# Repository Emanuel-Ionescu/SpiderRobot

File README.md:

## SpiderRobot

Check software and hardware branch

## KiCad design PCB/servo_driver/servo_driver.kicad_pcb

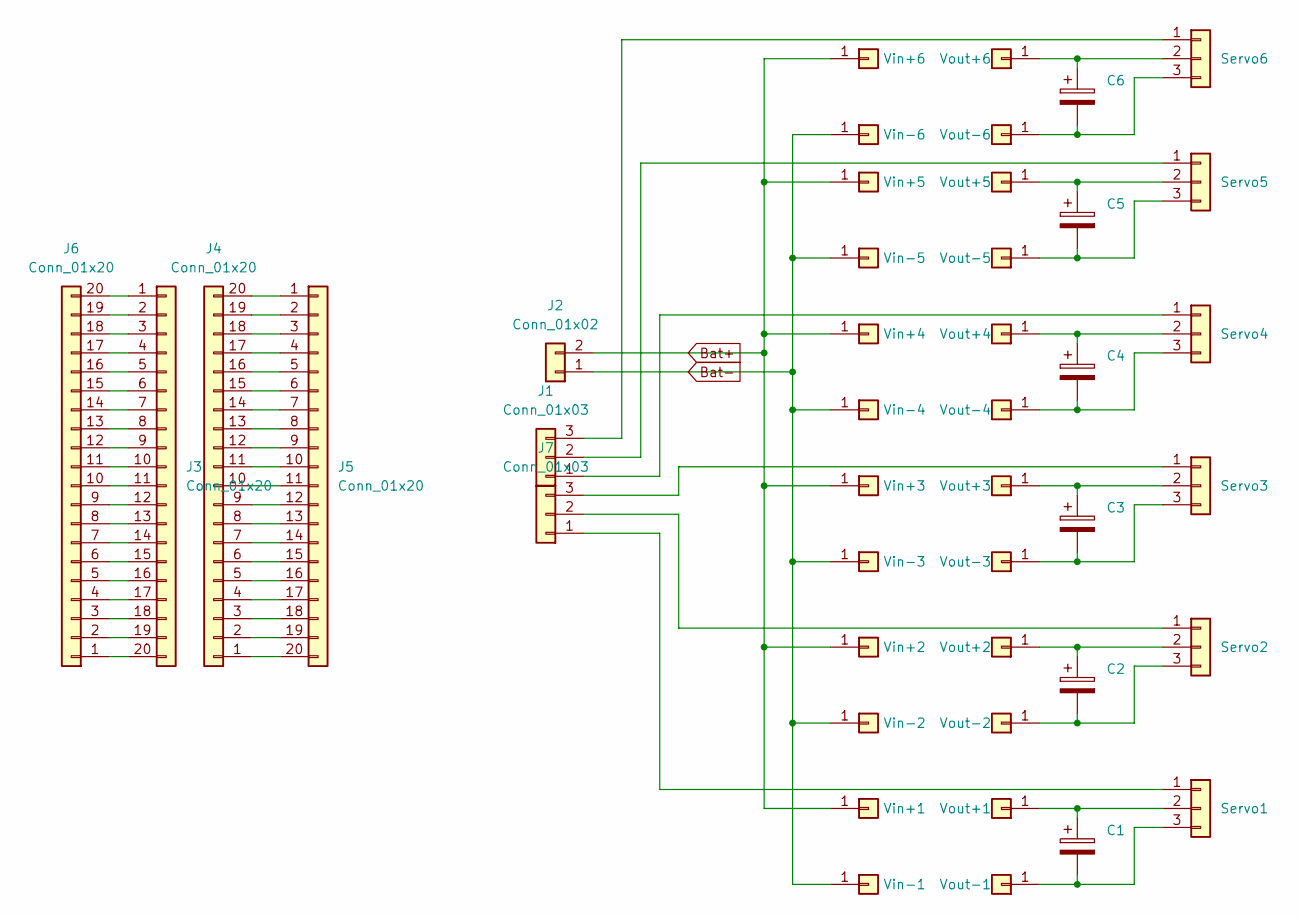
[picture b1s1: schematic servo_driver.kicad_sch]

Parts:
C1, C2, C3, C4, C5, C6: C_Polarized; CP_Radial_D5.0mm_P2.50mm
J1, J7: Conn_01x03; JST_PH_B3B-PH-K_1x03_P2.00mm_Vertical
J2: Conn_01x02; AMASS_XT60-M_1x02_P7.20mm_Vertical
J3, J4, J5, J6: Conn_01x20; PinHeader_1x20_P2.54mm_Vertical
Servo1, Servo2, Servo3, Servo4, Servo5, Servo6: Conn_01x03; PinSocket_1x03_P2.54mm_Vertical
Vin+1, Vin+2, Vin+3, Vin+4, Vin+5, Vin+6: Conn_01x01; PinHeader_1x01_P2.00mm_Vertical
Vin-1, Vin-2, Vin-3, Vin-4, Vin-5, Vin-6: Conn_01x01; PinHeader_1x01_P2.00mm_Vertical
Vout+1, Vout+2, Vout+3, Vout+4, Vout+5, Vout+6: Conn_01x01; PinHeader_1x01_P2.00mm_Vertical
Vout-1, Vout-2, Vout-3, Vout-4, Vout-5, Vout-6: Conn_01x01; PinHeader_1x01_P2.00mm_Vertical

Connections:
Bat+: J2.2, Vin+1.1, Vin+2.1, Vin+3.1, Vin+4.1, Vin+5.1, Vin+6.1
Bat-: J2.1, Vin-1.1, Vin-2.1, Vin-3.1, Vin-4.1, Vin-5.1, Vin-6.1
unnamed: J1.1, Servo4.1
unnamed: J1.2, Servo5.1
unnamed: J1.3, Servo6.1
unnamed: J3.1, J6.20
unnamed: J3.2, J6.19
unnamed: J3.3, J6.18
unnamed: J3.4, J6.17
unnamed: J3.5, J6.16
unnamed: J3.6, J6.15
unnamed: J3.7, J6.14
unnamed: J3.8, J6.13
unnamed: J3.9, J6.12
unnamed: J3.10, J6.11
unnamed: J3.11, J6.10
unnamed: J3.12, J6.9
unnamed: J3.13, J6.8
unnamed: J3.14, J6.7
unnamed: J3.15, J6.6
unnamed: J3.16, J6.5
unnamed: J3.17, J6.4
unnamed: J3.18, J6.3
unnamed: J3.19, J6.2
unnamed: J3.20, J6.1
unnamed: J4.1, J5.20
unnamed: J4.2, J5.19
unnamed: J4.3, J5.18
unnamed: J4.4, J5.17
unnamed: J4.5, J5.16
unnamed: J4.6, J5.15
unnamed: J4.7, J5.14
unnamed: J4.8, J5.13
unnamed: J4.9, J5.12
unnamed: J4.10, J5.11
unnamed: J4.11, J5.10
unnamed: J4.12, J5.9
unnamed: J4.13, J5.8
unnamed: J4.14, J5.7
unnamed: J4.15, J5.6
unnamed: J4.16, J5.5
unnamed: J4.17, J5.4
unnamed: J4.18, J5.3
unnamed: J4.19, J5.2
unnamed: J4.20, J5.1
unnamed: J7.1, Servo1.1
unnamed: J7.2, Servo2.1
unnamed: J7.3, Servo3.1
unnamed: C1.1, Servo1.2, Vout+1.1
unnamed: C1.2, Servo1.3, Vout-1.1
unnamed: C2.1, Servo2.2, Vout+2.1
unnamed: C2.2, Servo2.3, Vout-2.1
unnamed: C3.1, Servo3.2, Vout+3.1
unnamed: C3.2, Servo3.3, Vout-3.1
unnamed: C4.1, Servo4.2, Vout+4.1
unnamed: C4.2, Servo4.3, Vout-4.1
unnamed: C5.1, Servo5.2, Vout+5.1
unnamed: C5.2, Servo5.3, Vout-5.1
unnamed: C6.1, Servo6.2, Vout+6.1
unnamed: C6.2, Servo6.3, Vout-6.1

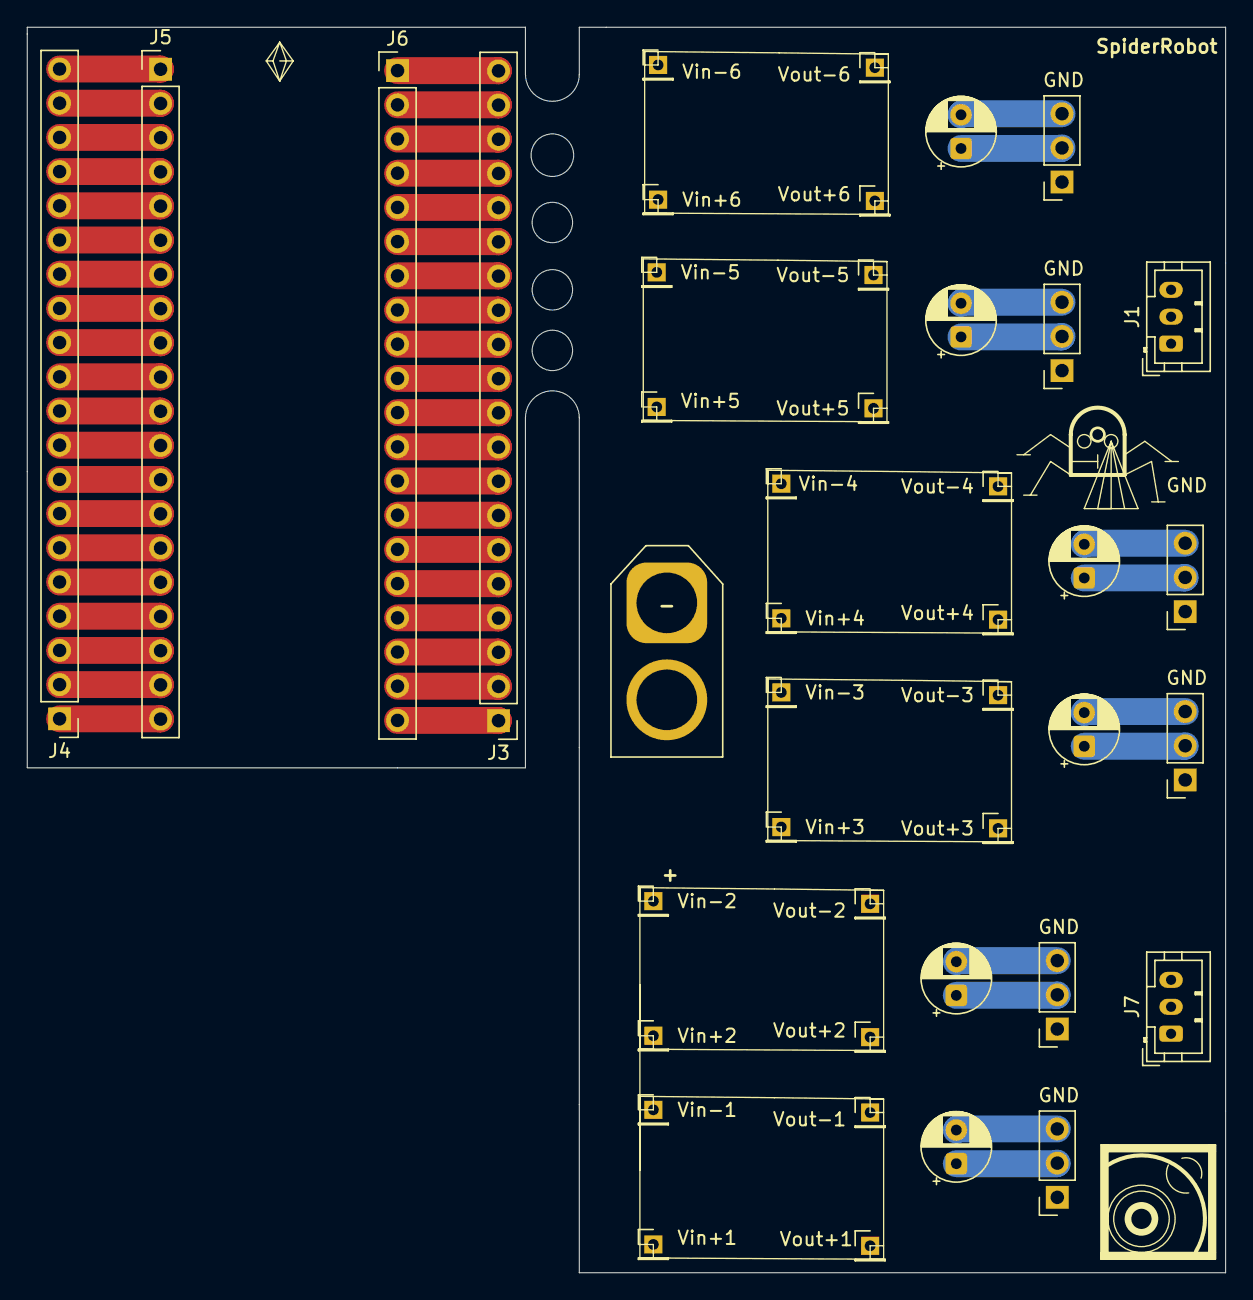
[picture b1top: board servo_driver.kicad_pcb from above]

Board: 2 copper layers, 89.0 x 92.5 mm, 43 parts (0 on the bottom side), 60 nets.

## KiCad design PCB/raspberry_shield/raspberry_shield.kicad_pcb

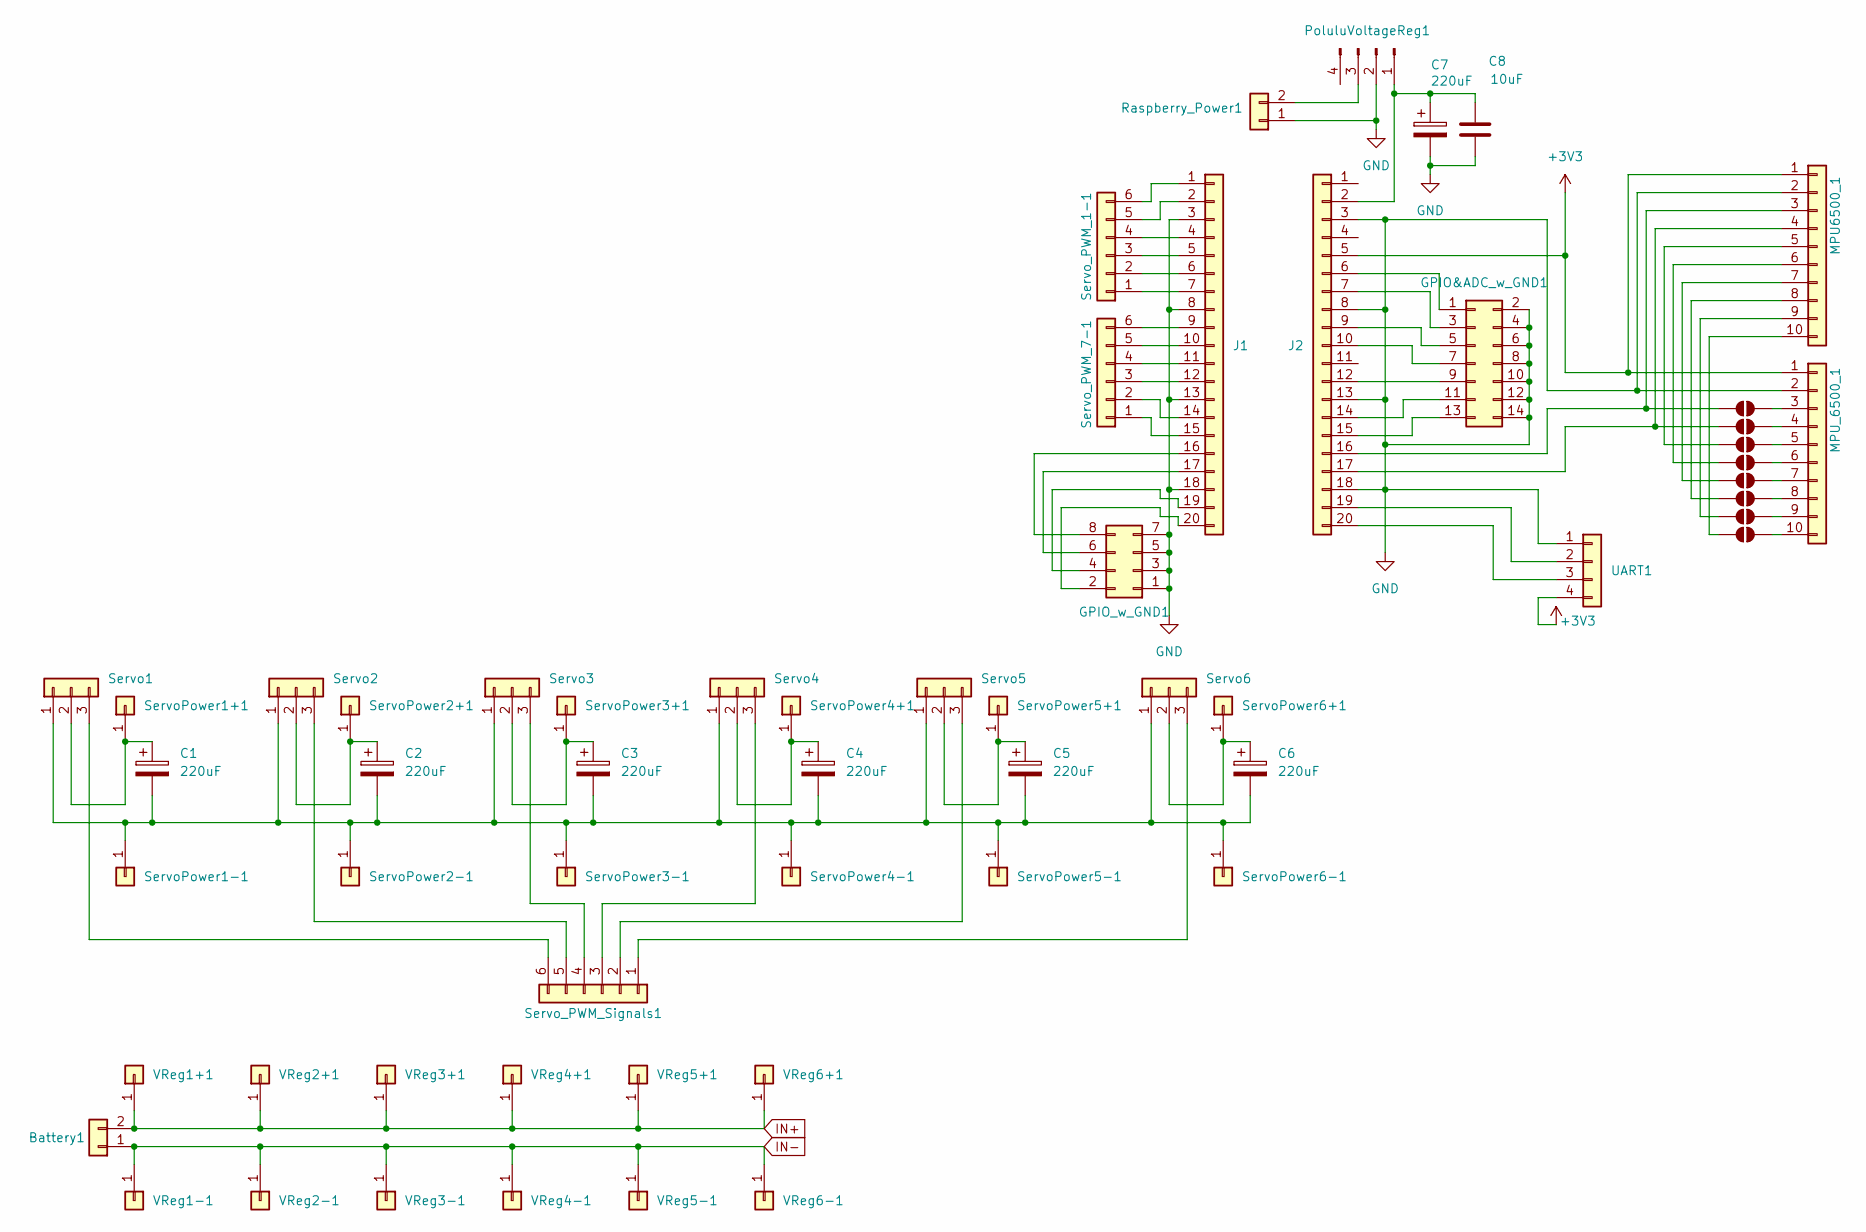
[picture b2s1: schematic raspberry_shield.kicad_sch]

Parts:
Battery1: Conn_01x02; AMASS_XT60-M_1x02_P7.20mm_Vertical
C1, C2, C3, C4, C5, C6, C7: 220uF; CP_Radial_D5.0mm_P2.50mm
C8: 10uF; C_0603_1608Metric
GPIO&ADC_w_GND1: Conn_02x07_Odd_Even; PinHeader_2x07_P2.54mm_Vertical
GPIO_w_GND1: Conn_02x04_Odd_Even; PinSocket_2x04_P2.54mm_Vertical
J1, J2: PinSocket_1x20_P2.54mm_Vertical
JP1, JP2, JP3, JP4, JP5, JP6, JP7, JP8: SolderJumper_2_Open; SolderJumper-2_P1.3mm_Open_RoundedPad1.0x1.5mm
MPU6500_1: Conn_01x10; PinHeader_1x10_P2.54mm_Vertical
MPU_6500_1: Conn_01x10; PinHeader_1x10_P2.54mm_Vertical
PoluluVoltageReg1: Voltage Reg; PinHeader_1x04_P2.54mm_Vertical
Raspberry_Power1: Conn_01x02; PinHeader_1x02_P2.54mm_Vertical
Servo1, Servo2, Servo3, Servo4, Servo5, Servo6: Conn_01x03; PinHeader_1x03_P2.54mm_Vertical
ServoPower1+1, ServoPower1-1, ServoPower2+1, ServoPower2-1, ServoPower3+1, ServoPower3-1, ServoPower4+1, ServoPower4-1, ServoPower5+1, ServoPower5-1, ServoPower6+1, ServoPower6-1: Conn_01x01; PinHeader_1x01_P2.54mm_Vertical
Servo_PWM_1-1: Conn_01x06; PinSocket_1x06_P2.54mm_Vertical
Servo_PWM_7-1: Servo_Signals_7-12; PinSocket_1x06_P2.54mm_Vertical
Servo_PWM_Signals1: Conn_01x06; PinSocket_1x06_P2.54mm_Vertical
UART1: Conn_01x04; PinHeader_1x04_P2.54mm_Vertical
VReg1+1, VReg1-1, VReg2+1, VReg2-1, VReg3+1, VReg3-1, VReg4+1, VReg4-1, VReg5+1, VReg5-1, VReg6+1, VReg6-1: Conn_01x01; PinHeader_1x01_P2.54mm_Vertical

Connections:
+3V3: J2.5, MPU6500_1.1, MPU_6500_1.1, UART1.4
GND: C7.2, C8.2, GPIO&ADC_w_GND1.2, GPIO&ADC_w_GND1.4, GPIO&ADC_w_GND1.6, GPIO&ADC_w_GND1.8, GPIO&ADC_w_GND1.10, GPIO&ADC_w_GND1.12, GPIO&ADC_w_GND1.14, GPIO_w_GND1.1, GPIO_w_GND1.3, GPIO_w_GND1.5, GPIO_w_GND1.7, J1.3, J1.8, J1.13, J1.18, J2.3, J2.8, J2.13, J2.18, MPU6500_1.2, MPU_6500_1.2, PoluluVoltageReg1.2, Raspberry_Power1.1, UART1.1
IN+: Battery1.2, VReg1+1.1, VReg2+1.1, VReg3+1.1, VReg4+1.1, VReg5+1.1, VReg6+1.1
IN-: Battery1.1, VReg1-1.1, VReg2-1.1, VReg3-1.1, VReg4-1.1, VReg5-1.1, VReg6-1.1
unnamed: GPIO&ADC_w_GND1.1, J2.6
unnamed: GPIO&ADC_w_GND1.3, J2.7
unnamed: GPIO&ADC_w_GND1.5, J2.9
unnamed: GPIO&ADC_w_GND1.7, J2.10
unnamed: GPIO&ADC_w_GND1.9, J2.12
unnamed: GPIO&ADC_w_GND1.11, J2.14
unnamed: GPIO&ADC_w_GND1.13, J2.15
unnamed: GPIO_w_GND1.2, J1.20
unnamed: GPIO_w_GND1.4, J1.19
unnamed: GPIO_w_GND1.6, J1.17
unnamed: GPIO_w_GND1.8, J1.16
unnamed: J1.1, Servo_PWM_1-1.6
unnamed: J1.2, Servo_PWM_1-1.5
unnamed: J1.4, Servo_PWM_1-1.4
unnamed: J1.5, Servo_PWM_1-1.3
unnamed: J1.6, Servo_PWM_1-1.2
unnamed: J1.7, Servo_PWM_1-1.1
unnamed: J1.9, Servo_PWM_7-1.6
unnamed: J1.10, Servo_PWM_7-1.5
unnamed: J1.11, Servo_PWM_7-1.4
unnamed: J1.12, Servo_PWM_7-1.3
unnamed: J1.14, Servo_PWM_7-1.2
unnamed: J1.15, Servo_PWM_7-1.1
unnamed: C7.1, C8.1, J2.2, PoluluVoltageReg1.1
unnamed: J2.16, JP1.1 (A), MPU6500_1.3
unnamed: J2.17, JP2.1 (A), MPU6500_1.4
unnamed: J2.19, UART1.2
unnamed: J2.20, UART1.3
unnamed: JP1.2 (B), MPU_6500_1.3
unnamed: JP2.2 (B), MPU_6500_1.4
unnamed: JP3.1 (A), MPU6500_1.5
unnamed: JP3.2 (B), MPU_6500_1.5
unnamed: JP4.1 (A), MPU6500_1.6
unnamed: JP4.2 (B), MPU_6500_1.6
unnamed: JP5.1 (A), MPU6500_1.7
unnamed: JP5.2 (B), MPU_6500_1.7
unnamed: JP6.1 (A), MPU6500_1.8
unnamed: JP6.2 (B), MPU_6500_1.8
unnamed: JP7.1 (A), MPU6500_1.9
unnamed: JP7.2 (B), MPU_6500_1.9
unnamed: JP8.1 (A), MPU6500_1.10
unnamed: JP8.2 (B), MPU_6500_1.10
unnamed: PoluluVoltageReg1.3, Raspberry_Power1.2
unnamed: C1.2, C2.2, C3.2, C4.2, C5.2, C6.2, Servo1.1, Servo2.1, Servo3.1, Servo4.1, Servo5.1, Servo6.1, ServoPower1-1.1, ServoPower2-1.1, ServoPower3-1.1, ServoPower4-1.1, ServoPower5-1.1, ServoPower6-1.1
unnamed: C1.1, Servo1.2, ServoPower1+1.1
unnamed: Servo1.3, Servo_PWM_Signals1.6
unnamed: C2.1, Servo2.2, ServoPower2+1.1
unnamed: Servo2.3, Servo_PWM_Signals1.5
unnamed: C3.1, Servo3.2, ServoPower3+1.1
unnamed: Servo3.3, Servo_PWM_Signals1.4
unnamed: C4.1, Servo4.2, ServoPower4+1.1
unnamed: Servo4.3, Servo_PWM_Signals1.3
unnamed: C5.1, Servo5.2, ServoPower5+1.1
unnamed: Servo5.3, Servo_PWM_Signals1.2
unnamed: C6.1, Servo6.2, ServoPower6+1.1
unnamed: Servo6.3, Servo_PWM_Signals1.1

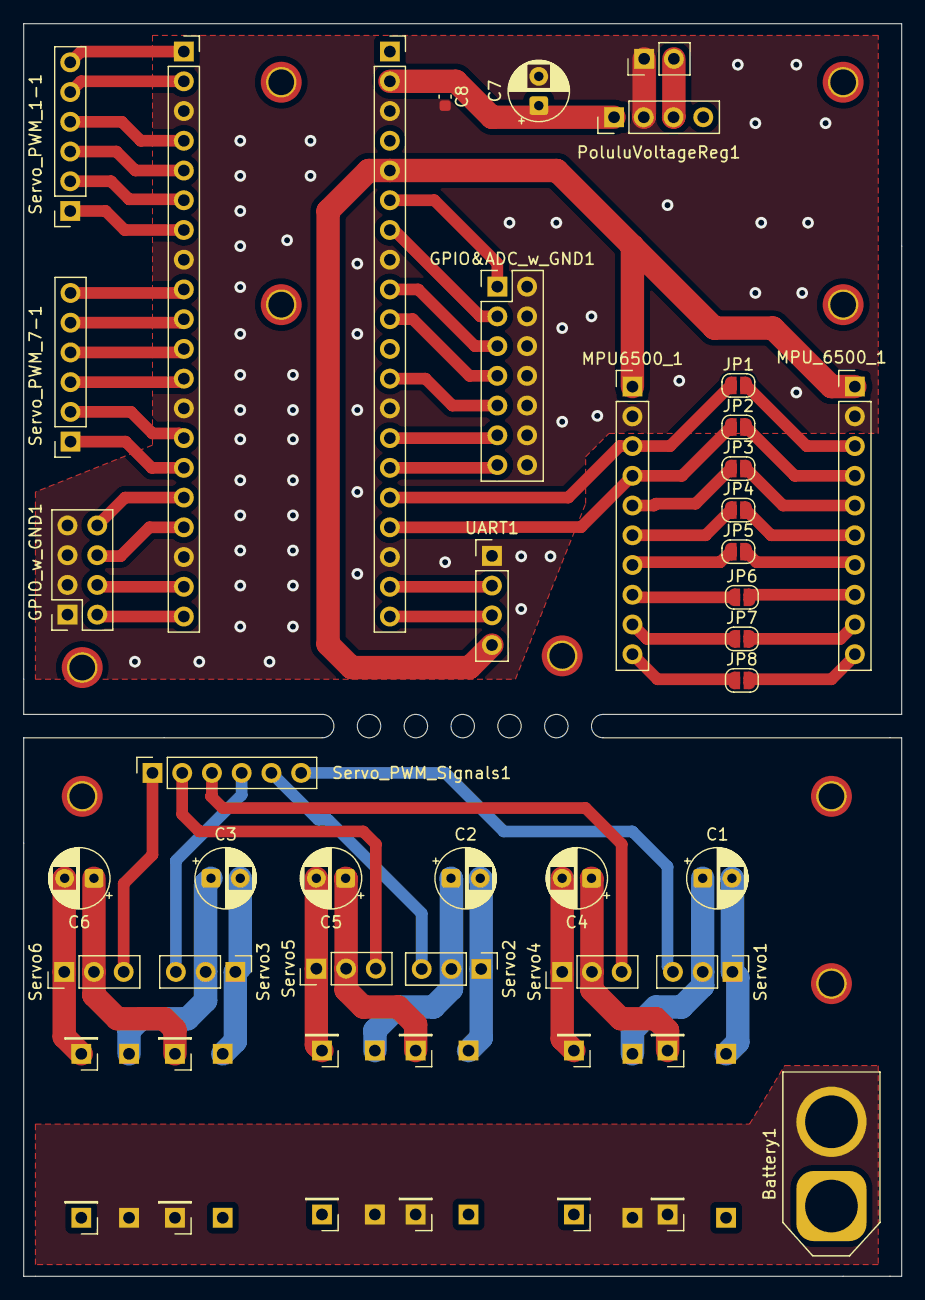
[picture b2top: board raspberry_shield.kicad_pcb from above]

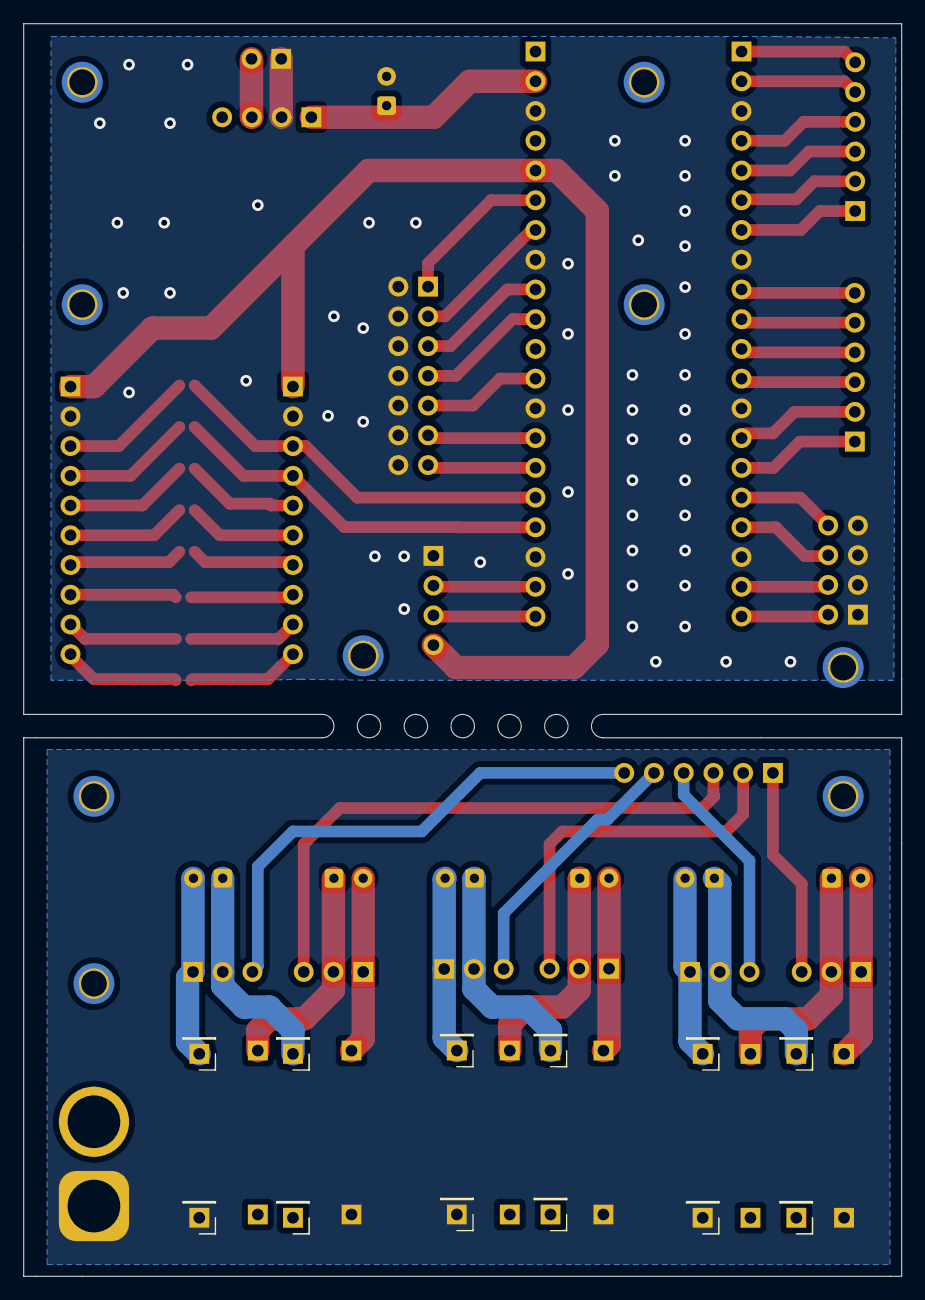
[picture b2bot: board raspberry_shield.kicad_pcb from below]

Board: 2 copper layers, 75.0 x 107.0 mm, 59 parts (12 on the bottom side), 60 nets.

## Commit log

2025-09-23 Inital Commit
2025-09-24 Manual Servo Control
2025-09-28 Manual control fixed
2025-09-29 Sequence feature start
2025-09-30 Remote control
2025-10-11 raspberry shield version 1
2025-10-11 Seqences with fixed positions
2025-11-08 Restructure of files
2025-12-03 Big Update
2025-12-03 3D models
2025-12-12 Serial comms
2025-12-12 updated hardware
2025-12-12 Branch for hardware
2025-12-12 Software branch
2025-12-12 Split in different branches
2025-12-22 Walking Sequence finished!
2025-12-22 Reuploaded Simulator (no modification to it)
2025-12-24 Hardware Update
2026-01-15 Unimportant hardware update
2026-01-15 Measurements of servos based on duty cycle
2026-01-15 PICO modifications on servo measuring
2026-01-20 servo calibration config file
2026-01-24 Servo calibration with both set_degree functions but with sign errors at servo 6 and 9
2026-01-27 Changed sign for troubled servos
2026-01-27 Updating method of calculating degrees
2026-04-09 FIRST REAL STEPS
2026-04-09 README
2026-04-09 Folder restructuring
2026-04-10 Hardware Updates
2026-04-10 Folder structure fix
2026-04-11 Experimental optimization
2026-04-11 Correct charts values
2026-04-11 time.sleep in while True loops
2026-04-11 Removed unused folders
2026-04-11 Optimal delay
2026-04-12 Turning sequences
2026-04-12 Turn update
2026-04-12 Correct turning sequence
2026-04-13 Gitignore
2026-04-15 Different delay for each sequence
2026-04-15 Fast mode
2026-04-20 Splitting the application in 2 parts: the sequences computing remains on PC to preserve battery
2026-05-18 Other updates
